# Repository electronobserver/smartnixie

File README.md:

<div align="center">

<span>━━━━━━ ⬢ ━━━━━━</span>

An ESP32-powered smart home Nixie Clock with customizable RGB backlighting, Wi-Fi connectivity, and a companion control app.

[About](#about) | [Guide](/) | [Credits](/)

---

(Display Board PCB)

(Control Board PCB)
</div>

# About

> [!WARNING]
> This project is currently a work in progress and as of now, no hardware has been tested. Take everything on this repository with a grain of salt. You can read up on this project's development process [here](https://electron.observer/posts/smartnixie).
>
# Credits
- **Symbols and Footprints:** [Nixies US](https://github.com/judge2005/Eagle-and-KiCAD-Nixie-Libs)
- **HV Power Supply:** [Tony Pottier (tonyp7)](https://github.com/tonyp7/170v-nixie-power-supply)

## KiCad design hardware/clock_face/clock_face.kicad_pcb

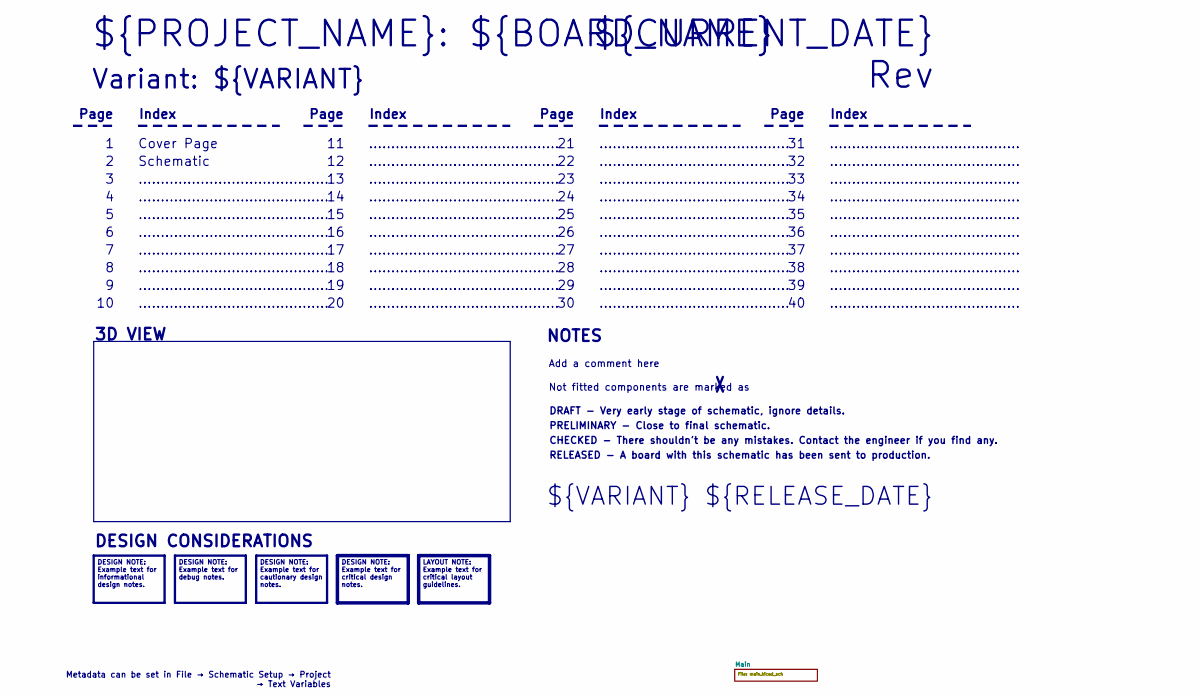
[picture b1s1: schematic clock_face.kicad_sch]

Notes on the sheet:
Metadata can be set in File → Schematic Setup → Project → Text Variables
DESIGN NOTE: Example text for informational design notes.
LAYOUT NOTE: Example text for critical layout guidelines.
DESIGN NOTE: Example text for cautionary design notes.
DESIGN NOTE: Example text for debug notes.
DESIGN NOTE: Example text for critical design notes.
...........................................
RELEASED - A board with this schematic has been sent to production.
Page
3D VIEW
Not fitted components are marked as
Index
PRELIMINARY - Close to final schematic.
${VARIANT} ${RELEASE_DATE}
${CURRENT_DATE}
Variant: ${VARIANT}
Rev ${REVISION}
${PROJECT_NAME}: ${BOARD_NAME}
DRAFT - Very early stage of schematic, ignore details.
Schematic
Add a comment here
Cover Page
NOTES
CHECKED - There shouldn't be any mistakes. Contact the engineer if you find any.
DESIGN CONSIDERATIONS

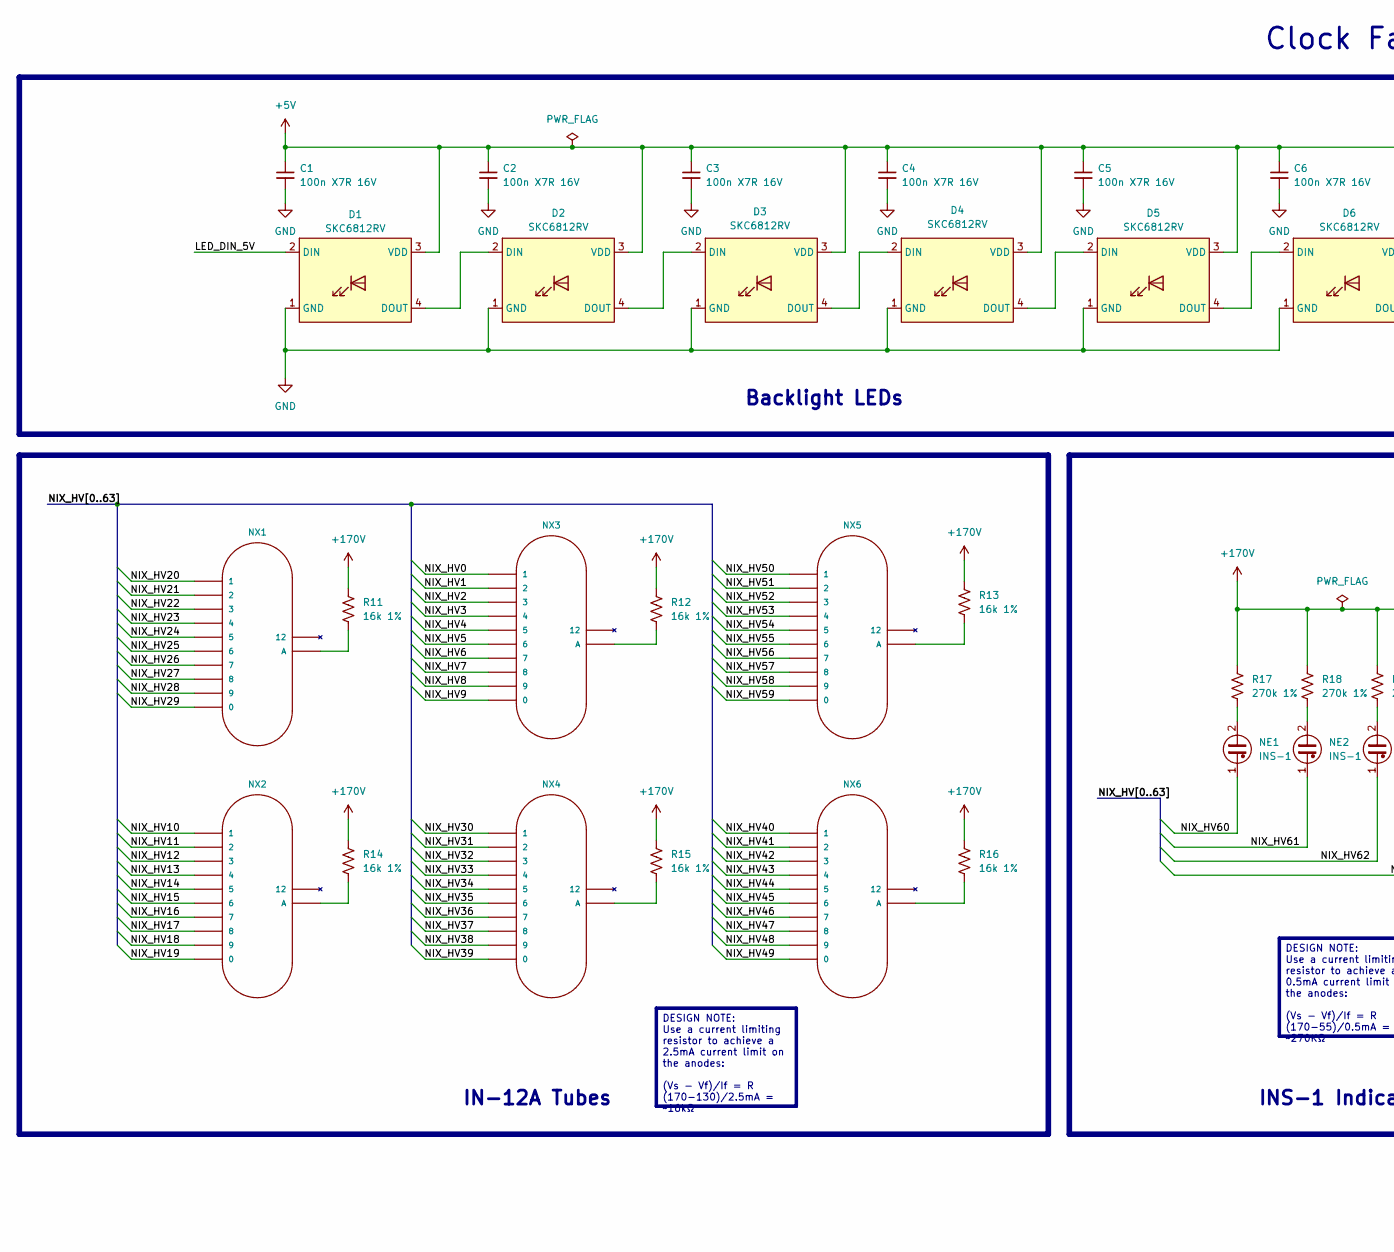
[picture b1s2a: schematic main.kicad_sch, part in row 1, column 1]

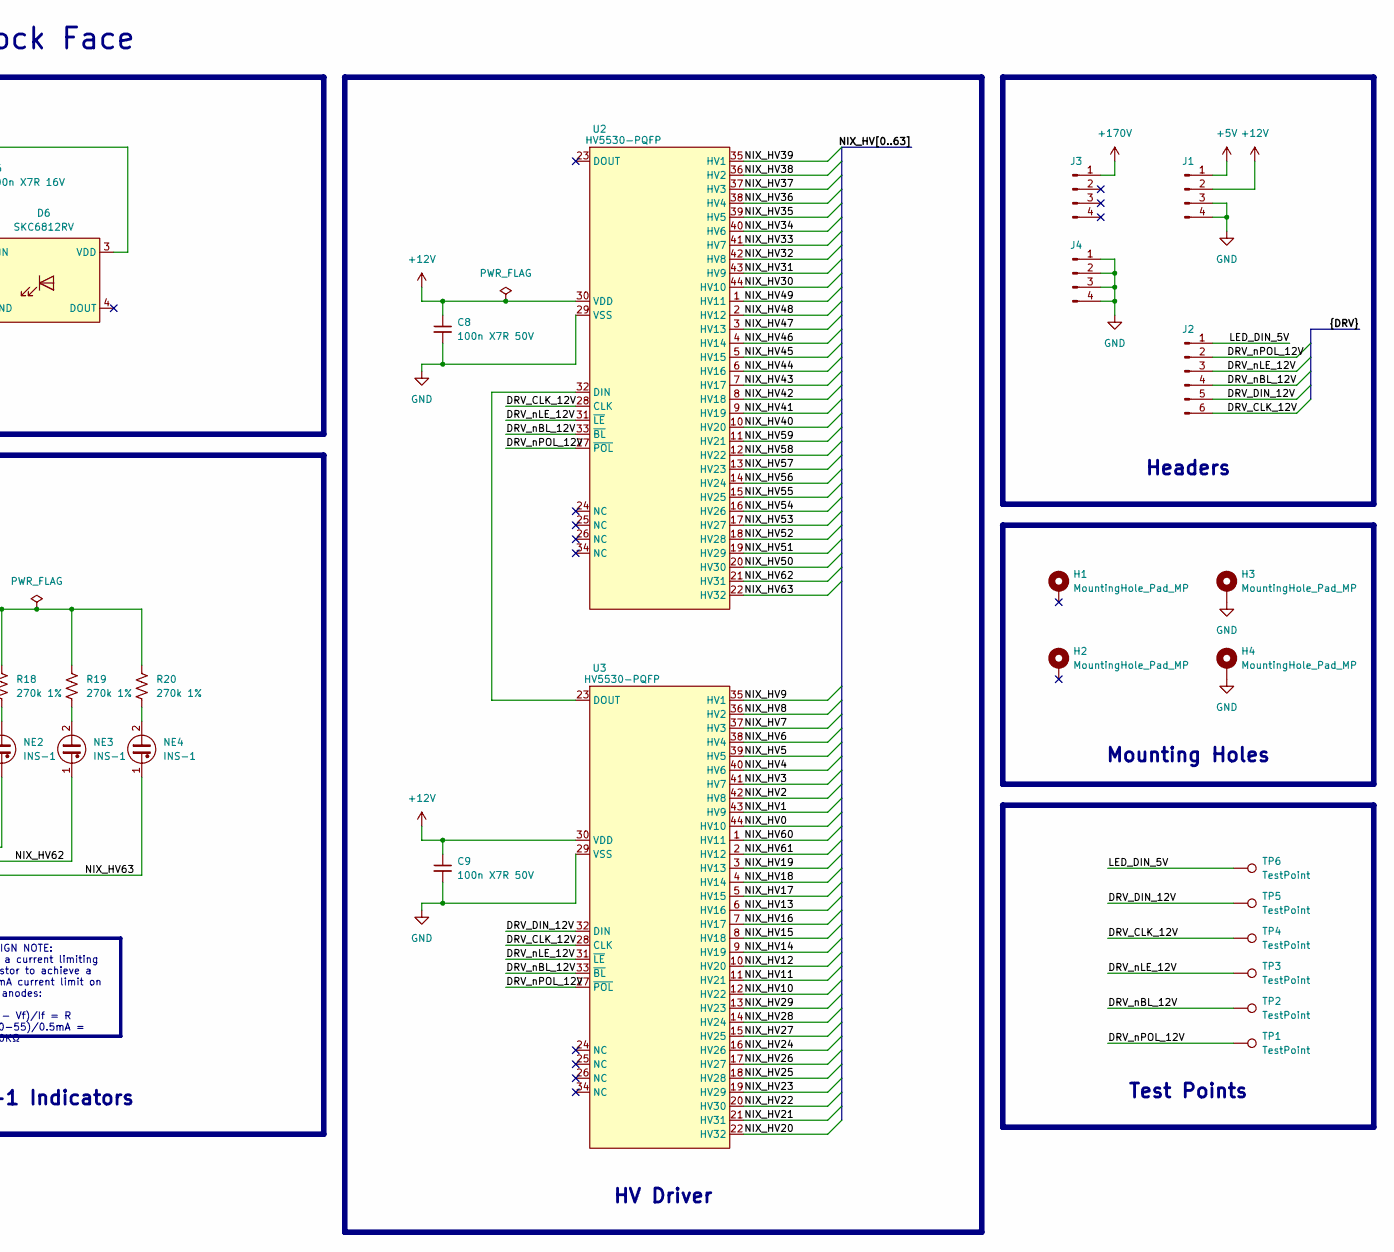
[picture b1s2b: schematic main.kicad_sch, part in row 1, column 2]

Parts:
C1, C2, C3, C4, C5, C6: 100n X7R 16V; C_0805_2012Metric_Pad1.18x1.45mm_HandSolder; Part No. CC0805KRX7R7BB104
C8, C9: 100n X7R 50V; C_0603_1608Metric_Pad1.08x0.95mm_HandSolder; Part No. CC0603KRX7R9BB104
D1, D2, D3, D4, D5, D6: SKC6812RV
H1, H2, H3, H4: MountingHole_Pad_MP; MountingHole_3.2mm_M3_Pad_Via
J1, J3, J4: Conn_01x04_Pin; PinHeader_1x04_P2.54mm_Vertical
J2: Conn_01x06_Pin; PinHeader_1x06_P2.54mm_Vertical
NE1, NE2, NE3, NE4: INS-1; INS_1
NX1, NX2, NX3, NX4, NX5, NX6: IN-12A; IN_12A
R11, R12, R13, R14, R15, R16: 16k 1%; R_1206_3216Metric_Pad1.30x1.75mm_HandSolder; Part No. RC1206FR-0716KL
R17, R18, R19, R20: 270k 1%; R_1206_3216Metric_Pad1.30x1.75mm_HandSolder; Part No. RC1206FR-07270KL
TP1, TP2, TP3, TP4, TP5, TP6: TestPoint; TestPoint_THTPad_D1.0mm_Drill0.5mm
U2, U3: HV5530-PQFP; PQFP-44_10x10mm_P0.8mm

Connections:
+5V: C1.1, C2.1, C3.1, C4.1, C5.1, C6.1, D1.3 (VDD), D2.3 (VDD), D3.3 (VDD), D4.3 (VDD), D5.3 (VDD), D6.3 (VDD), J1.1
+12V: C8.1, C9.1, J1.2, U2.30 (VDD), U3.30 (VDD)
+170V: J3.1, R11.1, R12.1, R13.1, R14.1, R15.1, R16.1, R17.1, R18.1, R19.1, R20.1
/Main/DRV_CLK_12V: J2.6, TP4.1, U2.28 (CLK), U3.28 (CLK)
/Main/DRV_DIN_12V: J2.5, TP5.1, U3.32 (DIN)
/Main/DRV_nBL_12V: J2.4, TP2.1, U2.33 (~BL), U3.33 (~BL)
/Main/DRV_nLE_12V: J2.3, TP3.1, U2.31 (~LE), U3.31 (~LE)
/Main/DRV_nPOL_12V: J2.2, TP1.1, U2.27 (~POL), U3.27 (~POL)
/Main/LED_DIN_5V: D1.2 (DIN), J2.1, TP6.1
/Main/NIX_HV0: NX3.11 (1), U3.44 (HV10)
/Main/NIX_HV1: NX3.10 (2), U3.43 (HV9)
/Main/NIX_HV2: NX3.9 (3), U3.42 (HV8)
/Main/NIX_HV3: NX3.8 (4), U3.41 (HV7)
/Main/NIX_HV4: NX3.7 (5), U3.40 (HV6)
/Main/NIX_HV5: NX3.6, U3.39 (HV5)
/Main/NIX_HV6: NX3.5 (7), U3.38 (HV4)
/Main/NIX_HV7: NX3.4 (8), U3.37 (HV3)
/Main/NIX_HV8: NX3.3 (9), U3.36 (HV2)
/Main/NIX_HV9: NX3.2 (0), U3.35 (HV1)
/Main/NIX_HV10: NX2.11 (1), U3.12 (HV22)
/Main/NIX_HV11: NX2.10 (2), U3.11 (HV21)
/Main/NIX_HV12: NX2.9 (3), U3.10 (HV20)
/Main/NIX_HV13: NX2.8 (4), U3.6 (HV16)
/Main/NIX_HV14: NX2.7 (5), U3.9 (HV19)
/Main/NIX_HV15: NX2.6, U3.8 (HV18)
/Main/NIX_HV16: NX2.5 (7), U3.7 (HV17)
/Main/NIX_HV17: NX2.4 (8), U3.5 (HV15)
/Main/NIX_HV18: NX2.3 (9), U3.4 (HV14)
/Main/NIX_HV19: NX2.2 (0), U3.3 (HV13)
/Main/NIX_HV20: NX1.11 (1), U3.22 (HV32)
/Main/NIX_HV21: NX1.10 (2), U3.21 (HV31)
/Main/NIX_HV22: NX1.9 (3), U3.20 (HV30)
/Main/NIX_HV23: NX1.8 (4), U3.19 (HV29)
/Main/NIX_HV24: NX1.7 (5), U3.16 (HV26)
/Main/NIX_HV25: NX1.6, U3.18 (HV28)
/Main/NIX_HV26: NX1.5 (7), U3.17 (HV27)
/Main/NIX_HV27: NX1.4 (8), U3.15 (HV25)
/Main/NIX_HV28: NX1.3 (9), U3.14 (HV24)
/Main/NIX_HV29: NX1.2 (0), U3.13 (HV23)
/Main/NIX_HV30: NX4.11 (1), U2.44 (HV10)
/Main/NIX_HV31: NX4.10 (2), U2.43 (HV9)
/Main/NIX_HV32: NX4.9 (3), U2.42 (HV8)
/Main/NIX_HV33: NX4.8 (4), U2.41 (HV7)
/Main/NIX_HV34: NX4.7 (5), U2.40 (HV6)
/Main/NIX_HV35: NX4.6, U2.39 (HV5)
/Main/NIX_HV36: NX4.5 (7), U2.38 (HV4)
/Main/NIX_HV37: NX4.4 (8), U2.37 (HV3)
/Main/NIX_HV38: NX4.3 (9), U2.36 (HV2)
/Main/NIX_HV39: NX4.2 (0), U2.35 (HV1)
/Main/NIX_HV40: NX6.11 (1), U2.10 (HV20)
/Main/NIX_HV41: NX6.10 (2), U2.9 (HV19)
/Main/NIX_HV42: NX6.9 (3), U2.8 (HV18)
/Main/NIX_HV43: NX6.8 (4), U2.7 (HV17)
/Main/NIX_HV44: NX6.7 (5), U2.6 (HV16)
/Main/NIX_HV45: NX6.6, U2.5 (HV15)
/Main/NIX_HV46: NX6.5 (7), U2.4 (HV14)
/Main/NIX_HV47: NX6.4 (8), U2.3 (HV13)
/Main/NIX_HV48: NX6.3 (9), U2.2 (HV12)
/Main/NIX_HV49: NX6.2 (0), U2.1 (HV11)
/Main/NIX_HV50: NX5.11 (1), U2.20 (HV30)
/Main/NIX_HV51: NX5.10 (2), U2.19 (HV29)
/Main/NIX_HV52: NX5.9 (3), U2.18 (HV28)
/Main/NIX_HV53: NX5.8 (4), U2.17 (HV27)
/Main/NIX_HV54: NX5.7 (5), U2.16 (HV26)
/Main/NIX_HV55: NX5.6, U2.15 (HV25)
/Main/NIX_HV56: NX5.5 (7), U2.14 (HV24)
/Main/NIX_HV57: NX5.4 (8), U2.13 (HV23)
/Main/NIX_HV58: NX5.3 (9), U2.12 (HV22)
/Main/NIX_HV59: NX5.2 (0), U2.11 (HV21)
/Main/NIX_HV60: NE1.1, U3.1 (HV11)
/Main/NIX_HV61: NE2.1, U3.2 (HV12)
/Main/NIX_HV62: NE3.1, U2.21 (HV31)
/Main/NIX_HV63: NE4.1, U2.22 (HV32)
GND: C1.2, C2.2, C3.2, C4.2, C5.2, C6.2, C8.2, C9.2, D1.1 (GND), D2.1 (GND), D3.1 (GND), D4.1 (GND), D5.1 (GND), D6.1 (GND), H3.1 (MP), H4.1 (MP), J1.3, J1.4, J4.1, J4.2, J4.3, J4.4, U2.29 (VSS), U3.29 (VSS)
unnamed: D1.4 (DOUT), D2.2 (DIN)
unnamed: D2.4 (DOUT), D3.2 (DIN)
unnamed: D3.4 (DOUT), D4.2 (DIN)
unnamed: D4.4 (DOUT), D5.2 (DIN)
unnamed: D5.4 (DOUT), D6.2 (DIN)
unnamed: NE1.2, R17.2
unnamed: NE2.2, R18.2
unnamed: NE3.2, R19.2
unnamed: NE4.2, R20.2
unnamed: NX1.1 (A), R11.2
unnamed: NX2.1 (A), R14.2
unnamed: NX3.1 (A), R12.2
unnamed: NX4.1 (A), R15.2
unnamed: NX5.1 (A), R13.2
unnamed: NX6.1 (A), R16.2
unnamed: U2.32 (DIN), U3.23 (DOUT)

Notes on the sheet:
HV Driver
Headers
DESIGN NOTE: Use a current limiting resistor to achieve a 2.5mA current limit on the anodes: (Vs - Vf)/If = R (170-130)/2.5mA = ~16kΩ
Test Points
Mounting Holes
INS-1 Indicators
DESIGN NOTE: Use a current limiting resistor to achieve a 0.5mA current limit on the anodes: (Vs - Vf)/If = R (170-55)/0.5mA = ~270KΩ
Backlight LEDs
Clock Face
IN-12A Tubes

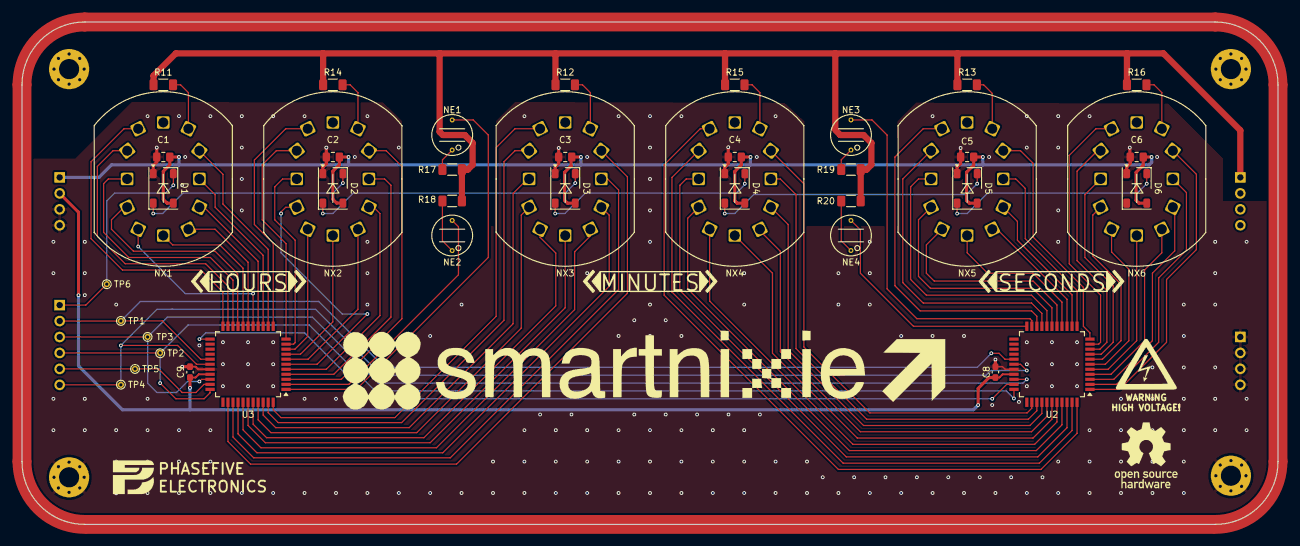
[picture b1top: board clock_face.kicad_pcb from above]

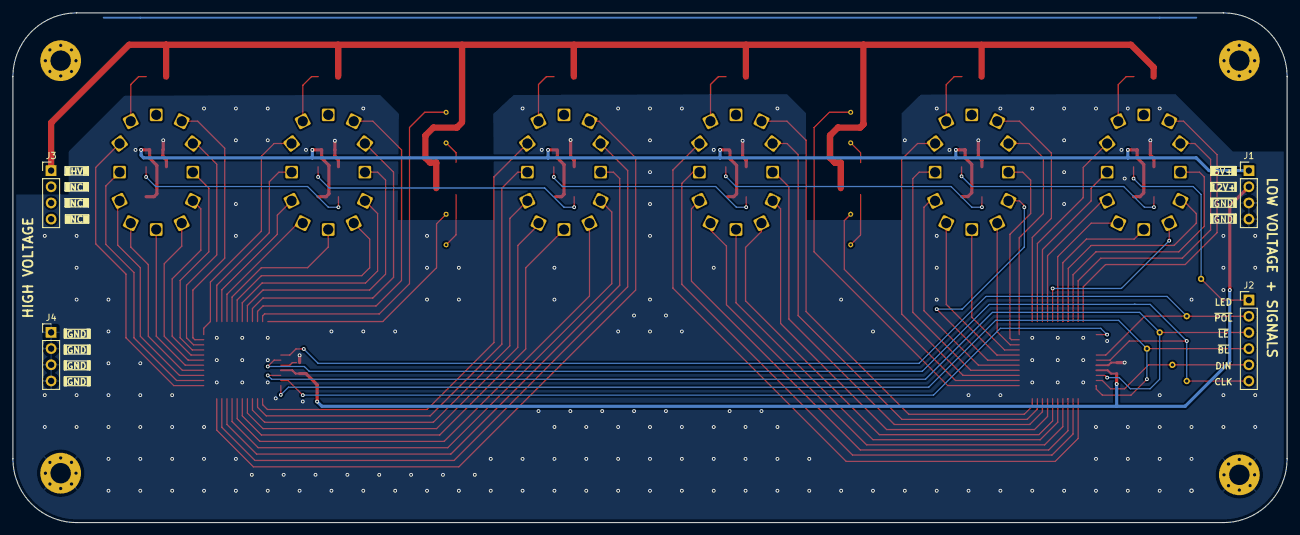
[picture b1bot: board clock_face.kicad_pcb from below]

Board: 2 copper layers, 200.0 x 80.0 mm, 56 parts (4 on the bottom side), 90 nets.

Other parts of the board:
G1: LOGO; SmartNixie
G2: LOGO; Arrow
G3: LOGO; OSHW
G5: LOGO; P5Logo
G5#2: LOGO; HV
G6: LOGO; AbstractDecal1

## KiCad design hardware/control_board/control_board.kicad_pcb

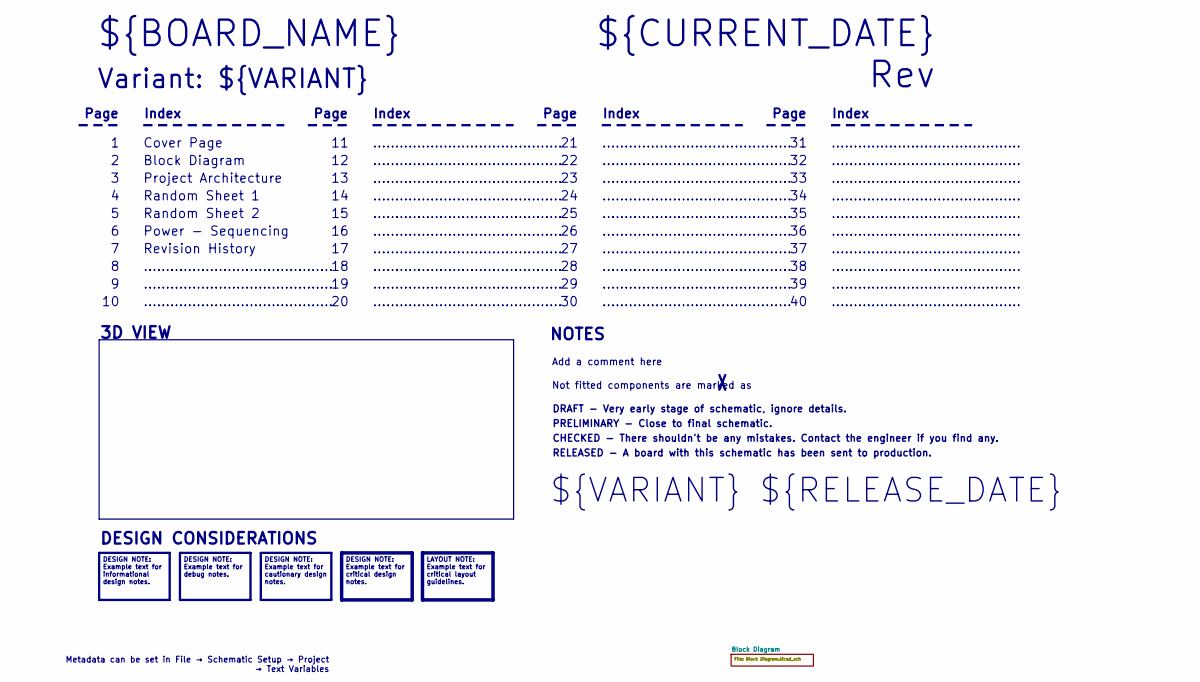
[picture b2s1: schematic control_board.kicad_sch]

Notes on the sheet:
Metadata can be set in File → Schematic Setup → Project → Text Variables
DESIGN NOTE: Example text for informational design notes.
LAYOUT NOTE: Example text for critical layout guidelines.
DESIGN NOTE: Example text for cautionary design notes.
DESIGN NOTE: Example text for debug notes.
DESIGN NOTE: Example text for critical design notes.
...........................................
RELEASED - A board with this schematic has been sent to production.
Page
3D VIEW
Not fitted components are marked as
Index
PRELIMINARY - Close to final schematic.
${VARIANT} ${RELEASE_DATE}
Random Sheet 1
${CURRENT_DATE}
Variant: ${VARIANT}
Rev ${REVISION}
Random Sheet 2
${BOARD_NAME}
DRAFT - Very early stage of schematic, ignore details.
Power - Sequencing
Block Diagram
Add a comment here
Cover Page
NOTES
Project Architecture
CHECKED - There shouldn't be any mistakes. Contact the engineer if you find any.
DESIGN CONSIDERATIONS
Revision History

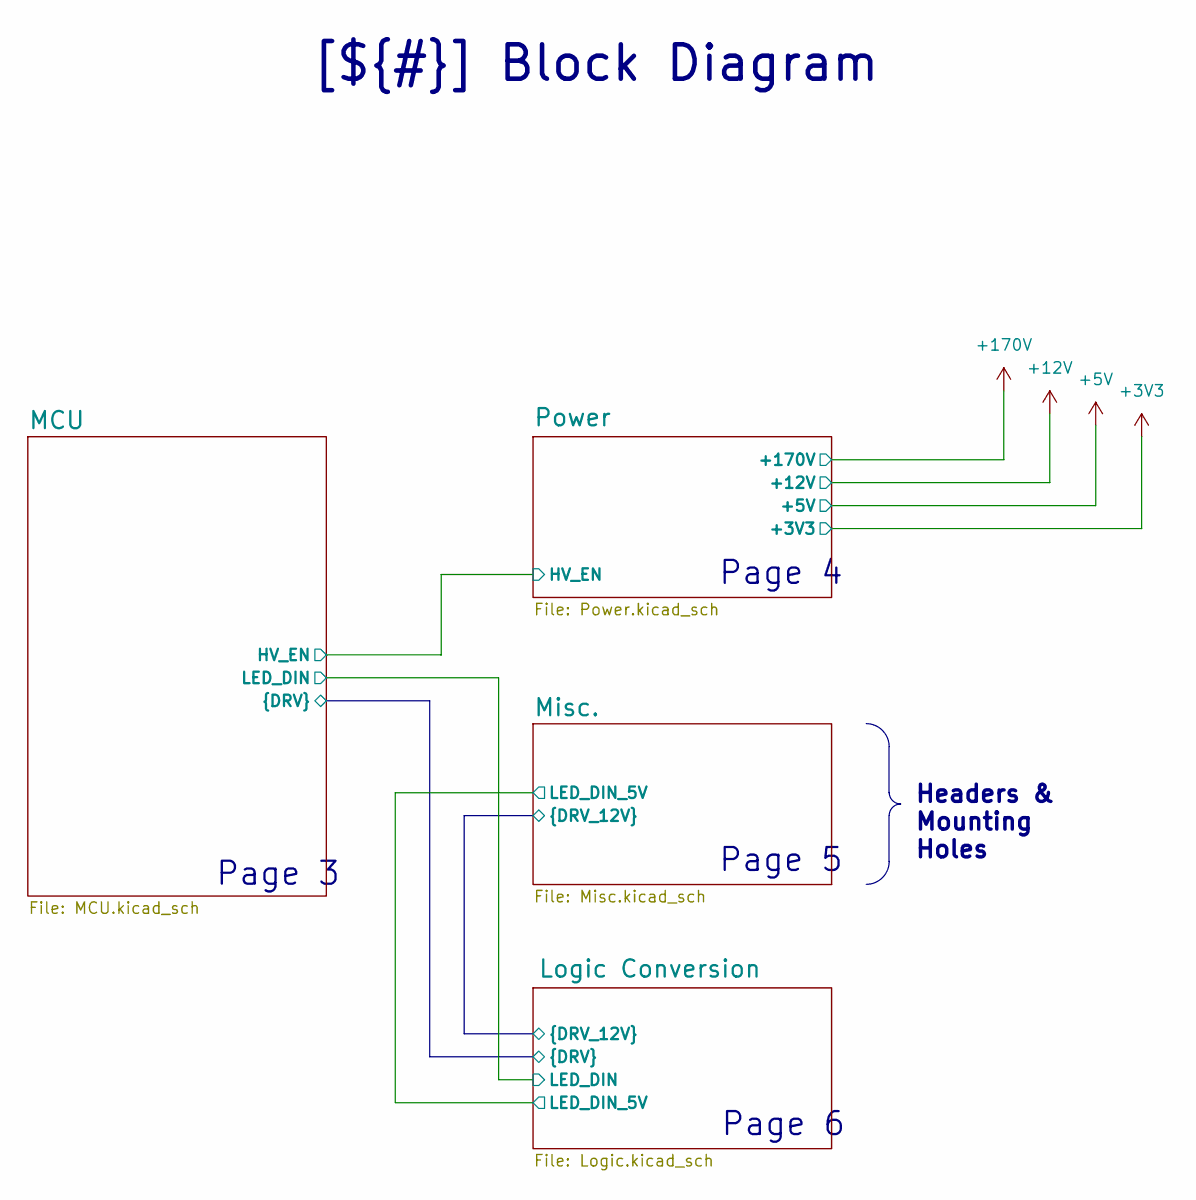
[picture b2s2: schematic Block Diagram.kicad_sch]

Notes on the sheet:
Headers & Mounting Holes
[${#}] Block Diagram
Page 6
Page 3
Page 5
Page 4

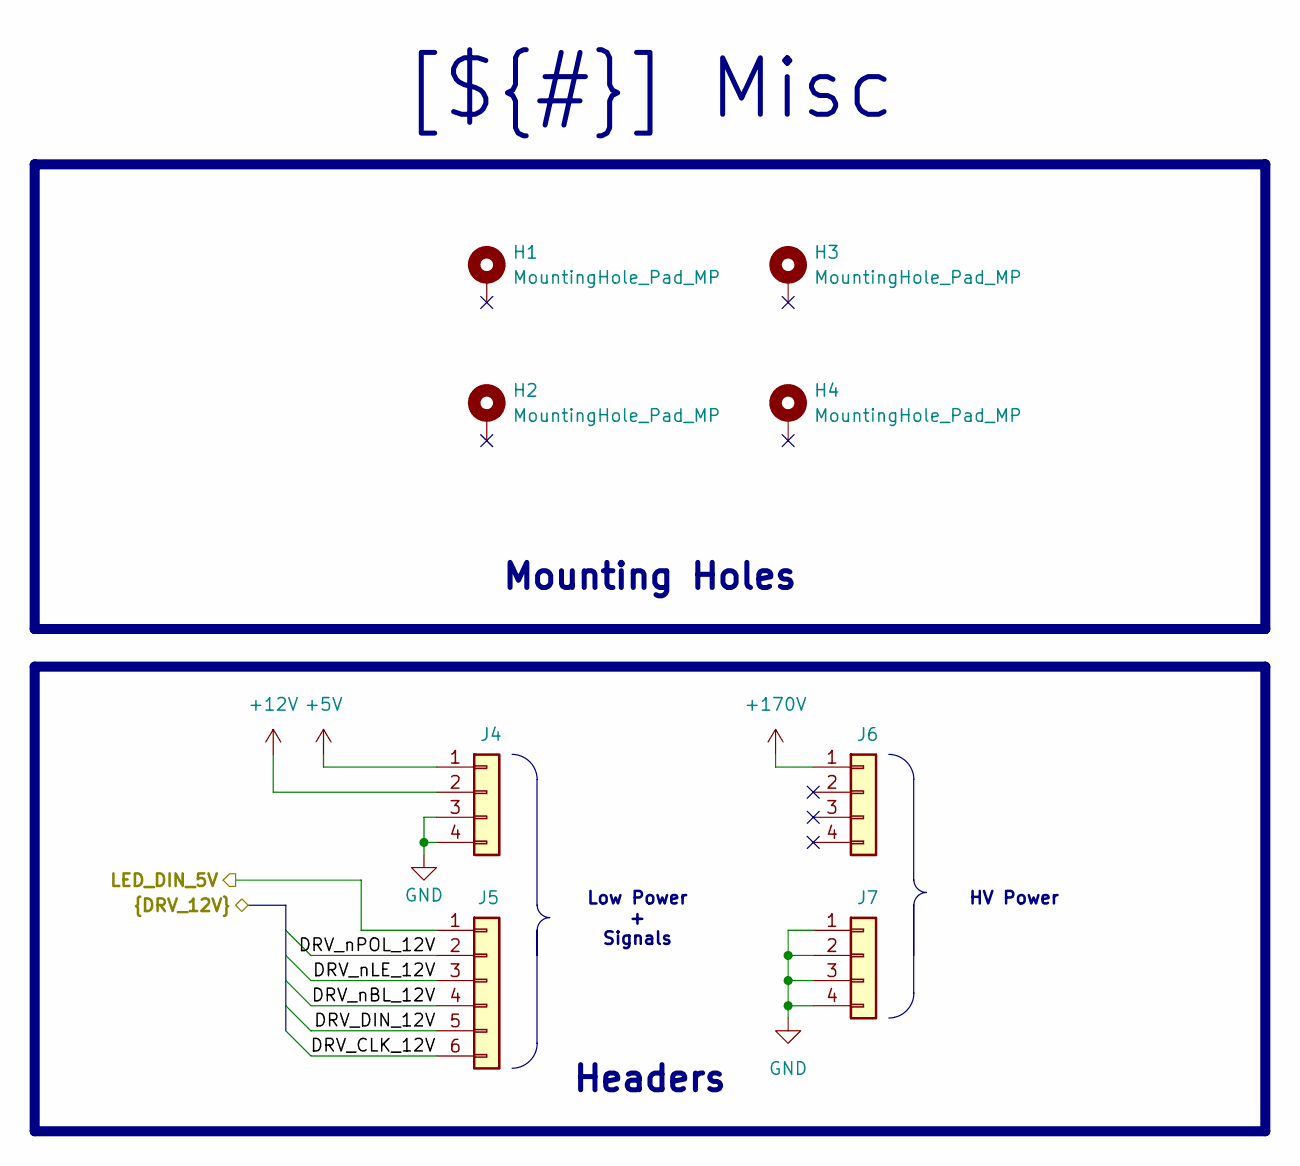
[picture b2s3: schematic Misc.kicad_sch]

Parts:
H1, H2, H3, H4: MountingHole_Pad_MP; MountingHole_3.2mm_M3_Pad_Via
J4, J6, J7: Conn_01x08; PinSocket_1x04_P2.54mm_Vertical
J5: Conn_01x08; PinSocket_1x06_P2.54mm_Vertical

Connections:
+5V: J4.1; also elsewhere on the board
+12V: J4.2; also elsewhere on the board
+170V: J6.1; also elsewhere on the board
/Block Diagram/Logic Conversion/DRV_CLK_12V: J5.6; also elsewhere on the board
/Block Diagram/Logic Conversion/DRV_DIN_12V: J5.5; also elsewhere on the board
/Block Diagram/Logic Conversion/DRV_nBL_12V: J5.4; also elsewhere on the board
/Block Diagram/Logic Conversion/DRV_nLE_12V: J5.3; also elsewhere on the board
/Block Diagram/Logic Conversion/DRV_nPOL_12V: J5.2; also elsewhere on the board
/Block Diagram/Logic Conversion/LED_DIN_5V: J5.1; also elsewhere on the board
GND: J4.3, J4.4, J7.1, J7.2, J7.3, J7.4; also elsewhere on the board

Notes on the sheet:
Low Power + Signals
Headers
Mounting Holes
HV Power
[${#}] ${TITLE}

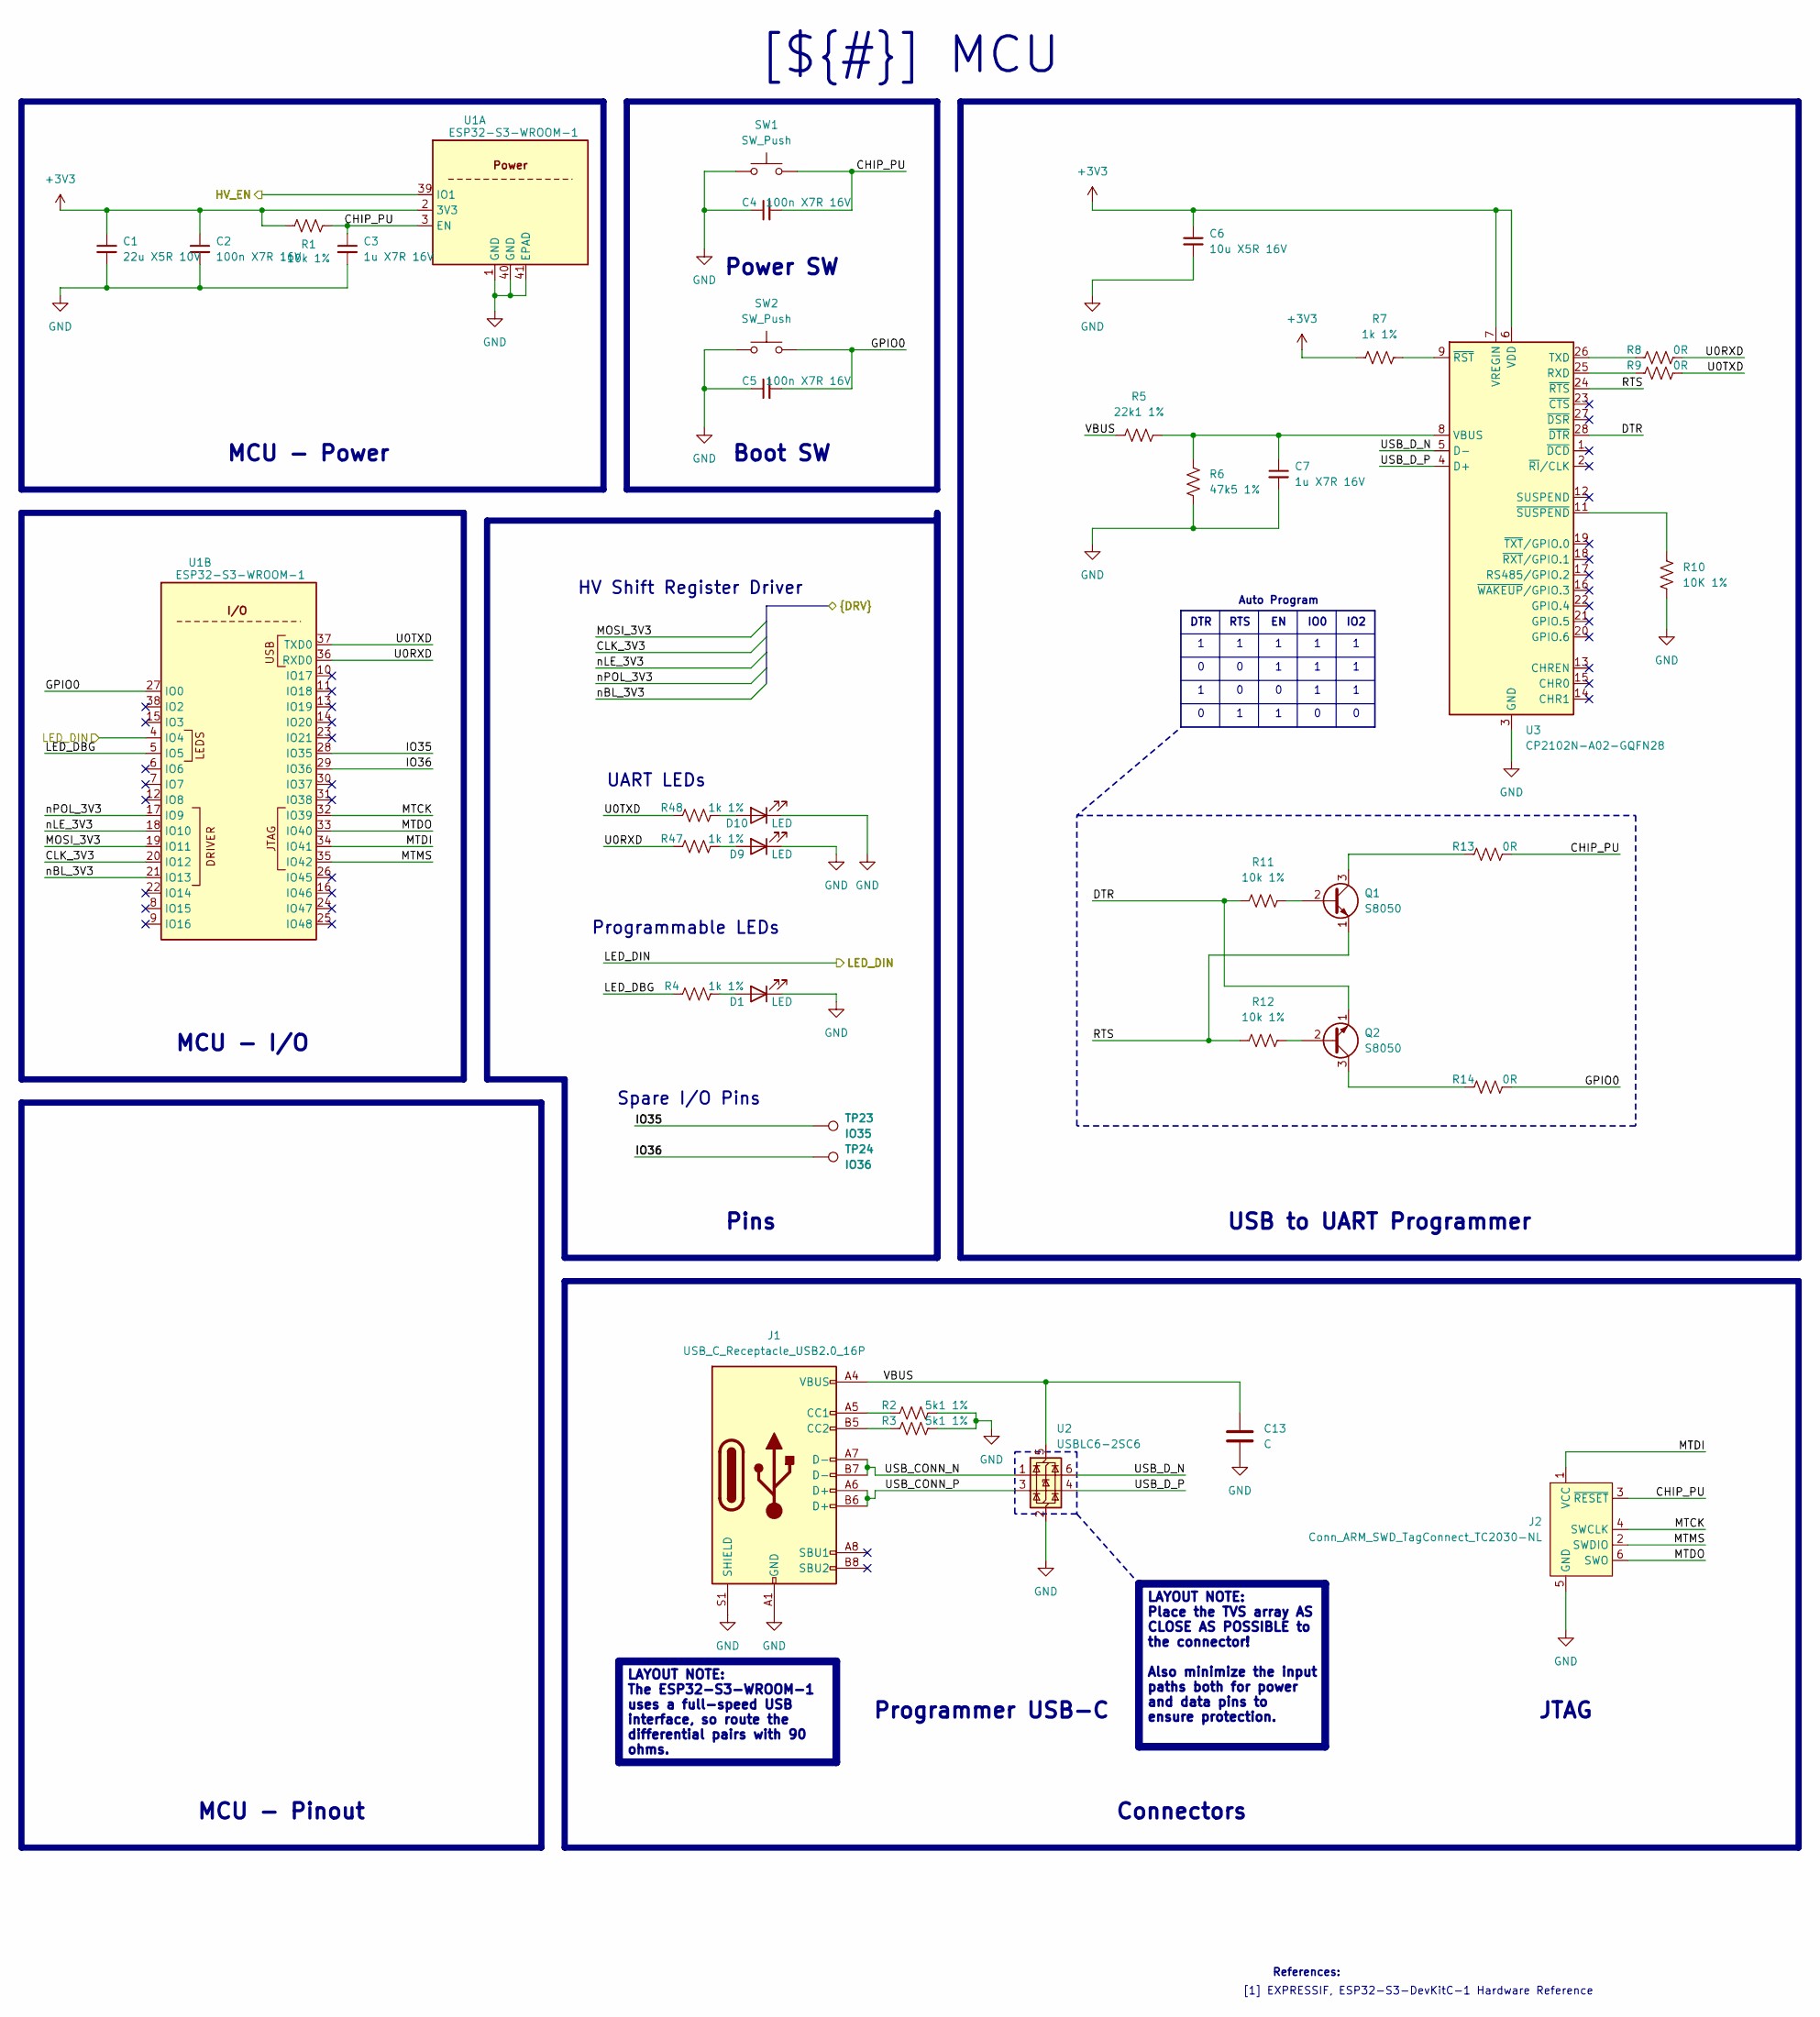
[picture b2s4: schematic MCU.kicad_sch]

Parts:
C1: 22u X5R 10V; C_0805_2012Metric; Part No. CL21A226MPQNNNE
C2, C4, C5: 100n X7R 16V; C_0805_2012Metric_Pad1.18x1.45mm_HandSolder; Part No. CC0805KRX7R7BB104
C3, C7: 1u X7R 16V; C_0805_2012Metric_Pad1.18x1.45mm_HandSolder; Part No. GRM21BR71C105KA01L
C6: 10u X5R 16V; C_0805_2012Metric_Pad1.18x1.45mm_HandSolder; Part No. GRM21BR61C106KE15K
C13: C
D1, D9, D10: LED; LED_0402_1005Metric_Pad0.77x0.64mm_HandSolder; Part No. VLMG1500-GS08
J1: USB_C_Receptacle_USB2.0_16P; USB_C_Receptacle_HRO_TYPE-C-31-M-12; Part No. 10155435-00011LF
J2: Conn_ARM_SWD_TagConnect_TC2030-NL; Tag-Connect_TC2030-IDC-NL_2x03_P1.27mm_Vertical
Q1, Q2: S8050; SOT-23_Handsoldering
R1, R11, R12: 10k 1%; R_0402_1005Metric_Pad0.72x0.64mm_HandSolder; Part No. AC0402FR-07107KL
R2, R3: 5k1 1%; R_0402_1005Metric_Pad0.72x0.64mm_HandSolder; Part No. RMCF0402FT4K75
R4, R7, R47, R48: 1k 1%; R_0402_1005Metric_Pad0.72x0.64mm_HandSolder; Part No. ERJ-2RKF1001X
R5: 22k1 1%; R_0402_1005Metric_Pad0.72x0.64mm_HandSolder; Part No. ERA-2ARB223X
R6: 47k5 1%; R_0402_1005Metric_Pad0.72x0.64mm_HandSolder; Part No. AC0402FR-0747K5L
R8, R9, R13, R14: 0R; R_0402_1005Metric_Pad0.72x0.64mm_HandSolder; Part No. RC0402JR-070RL
R10: 10K 1%; R_0402_1005Metric_Pad0.72x0.64mm_HandSolder; Part No. AC0402FR-07107KL
SW1, SW2: SW_Push; SW_SPST_TL3342
TP23: IO35; TestPoint_Pad_D1.0mm
TP24: IO36; TestPoint_Pad_D1.0mm
U1: ESP32-S3-WROOM-1
U2: USBLC6-2SC6; SOT-23-6
U3: CP2102N-A02-GQFN28; QFN-28-1EP_5x5mm_P0.5mm_EP3.35x3.35mm

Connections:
+3V3: C1.1, C2.1, C6.1, R1.1, R7.1, U1.2 (3V3), U3.6 (VDD), U3.7 (VREGIN); also elsewhere on the board
/Block Diagram/Logic Conversion/CLK_3V3: U1.20 (IO12); also elsewhere on the board
/Block Diagram/Logic Conversion/MOSI_3V3: U1.19 (IO11); also elsewhere on the board
/Block Diagram/Logic Conversion/nBL_3V3: U1.21 (IO13); also elsewhere on the board
/Block Diagram/Logic Conversion/nLE_3V3: U1.18 (IO10); also elsewhere on the board
/Block Diagram/Logic Conversion/nPOL_3V3: U1.17 (IO9); also elsewhere on the board
/Block Diagram/MCU/CHIP_PU: C3.1, C4.2, J2.3 (~RESET), R1.2, R13.2, SW1.2, U1.3 (EN)
/Block Diagram/MCU/DTR: Q2.1 (E), R11.1, U3.28 (~DTR)
/Block Diagram/MCU/GPIO0: C5.2, R14.2, SW2.2, U1.27 (IO0)
/Block Diagram/MCU/HV_EN: U1.39 (IO1); also elsewhere on the board
/Block Diagram/MCU/IO35: TP23.1, U1.28 (IO35)
/Block Diagram/MCU/IO36: TP24.1, U1.29 (IO36)
/Block Diagram/MCU/LED_DBG: R4.1, U1.5 (IO5)
/Block Diagram/MCU/LED_DIN: U1.4 (IO4); also elsewhere on the board
/Block Diagram/MCU/MTCK: J2.4 (SWCLK), U1.32 (IO39)
/Block Diagram/MCU/MTDI: J2.1 (VCC), U1.34 (IO41)
/Block Diagram/MCU/MTDO: J2.6 (SWO), U1.33 (IO40)
/Block Diagram/MCU/MTMS: J2.2 (SWDIO), U1.35 (IO42)
/Block Diagram/MCU/RTS: Q1.1 (E), R12.1, U3.24 (~RTS)
/Block Diagram/MCU/U0RXD: R8.2, R47.1, U1.36 (RXD0)
/Block Diagram/MCU/U0TXD: R9.2, R48.1, U1.37 (TXD0)
/Block Diagram/MCU/USB_CONN_N: J1.A7 (D-), J1.B7 (D-), U2.1 (I/O1)
/Block Diagram/MCU/USB_CONN_P: J1.A6 (D+), J1.B6 (D+), U2.3 (I/O2)
/Block Diagram/MCU/USB_D_N: U2.6 (I/O1), U3.5 (D-)
/Block Diagram/MCU/USB_D_P: U2.4 (I/O2), U3.4 (D+)
/Block Diagram/MCU/VBUS: C13.1, J1.A4 (VBUS), J1.A9 (VBUS), J1.B4 (VBUS), J1.B9 (VBUS), R5.1, U2.5 (VBUS)
GND: C1.2, C2.2, C3.2, C4.1, C5.1, C6.2, C7.2, C13.2, D1.1 (K), D9.1 (K), D10.1 (K), J1.A1 (GND), J1.A12 (GND), J1.B1 (GND), J1.B12 (GND), J1.S1 (SHIELD), J2.5 (GND), R2.2, R3.2, R6.1, R10.2, SW1.1, SW2.1, U1.1 (GND), U1.40 (GND), U1.41 (EPAD), U2.2 (GND), U3.3 (GND), U3.29 (GND); also elsewhere on the board
unnamed: D1.2 (A), R4.2
unnamed: D9.2 (A), R47.2
unnamed: D10.2 (A), R48.2
unnamed: J1.A5 (CC1), R2.1
unnamed: J1.B5 (CC2), R3.1
unnamed: Q1.2 (B), R11.2
unnamed: Q1.3 (C), R13.1
unnamed: Q2.2 (B), R12.2
unnamed: Q2.3 (C), R14.1
unnamed: R9.1, U3.25 (RXD)
unnamed: R8.1, U3.26 (TXD)
unnamed: C7.1, R5.2, R6.2, U3.8 (VBUS)
unnamed: R7.2, U3.9 (~RST)
unnamed: R10.1, U3.11 (~SUSPEND)

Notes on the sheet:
USB to UART Programmer
LAYOUT NOTE: The ESP32-S3-WROOM-1 uses a full-speed USB interface, so route the differential pairs with 90 ohms.
MCU - I/O
LAYOUT NOTE: Place the TVS array AS CLOSE AS POSSIBLE to the connector! Also minimize the input paths both for power and data pins to ensure protection.
[${#}] ${TITLE}
Boot SW
Pins
Power SW
MCU - Power
MCU - Pinout
Programmer USB-C
Connectors
JTAG
UART LEDs
RTS
References:
[1] EXPRESSIF, ESP32-S3-DevKitC-1 Hardware Reference
IO0
Auto Program
HV Shift Register Driver
DTR
Spare I/O Pins
Programmable LEDs
IO2
